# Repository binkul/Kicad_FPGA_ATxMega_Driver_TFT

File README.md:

# Kicad_FPGA_ATxMega_Driver_TFT

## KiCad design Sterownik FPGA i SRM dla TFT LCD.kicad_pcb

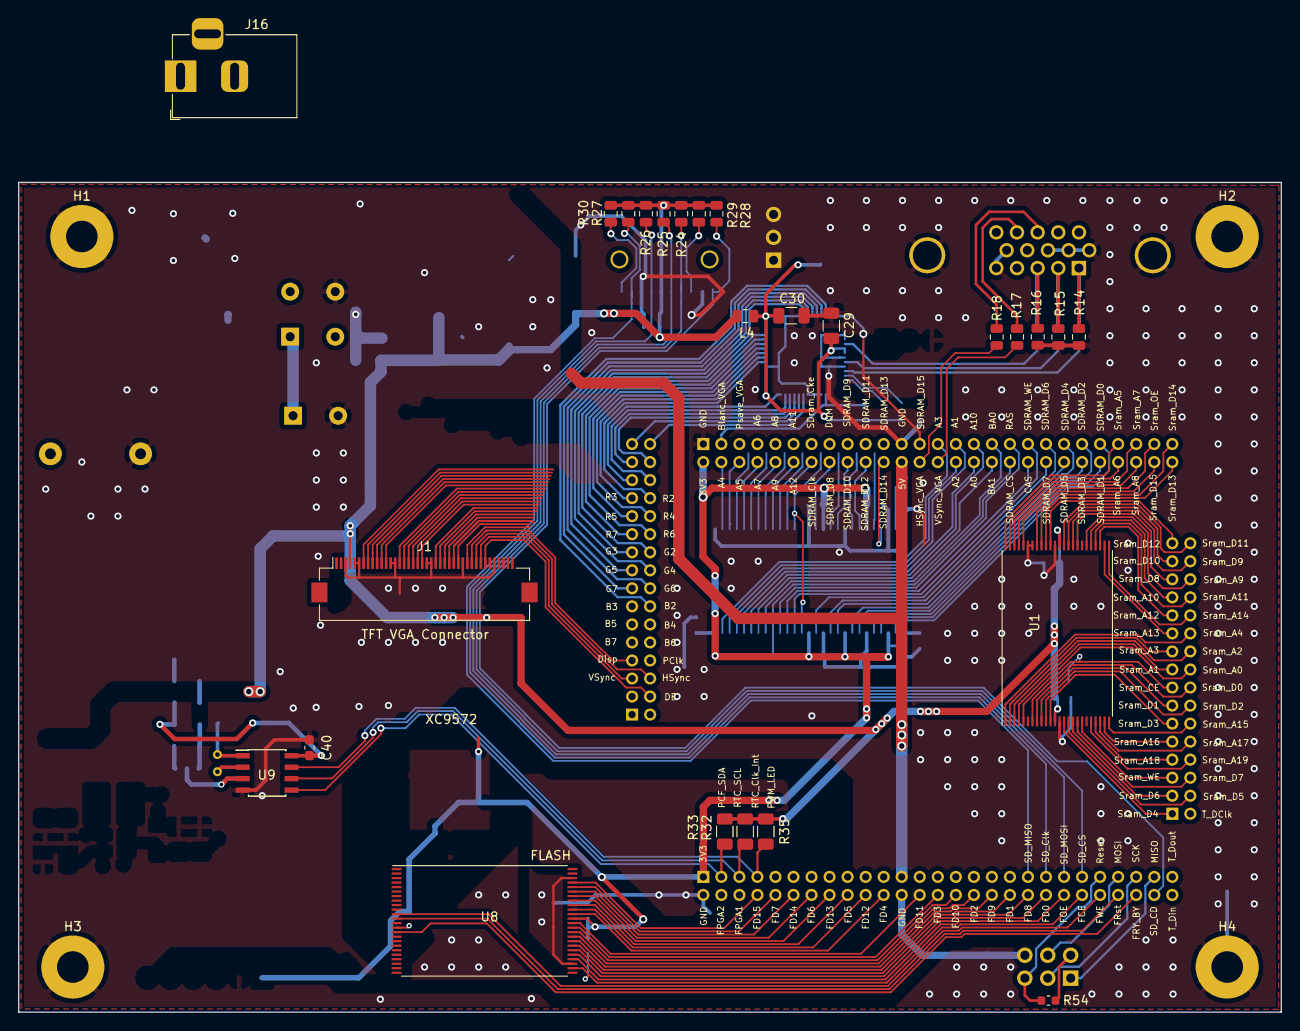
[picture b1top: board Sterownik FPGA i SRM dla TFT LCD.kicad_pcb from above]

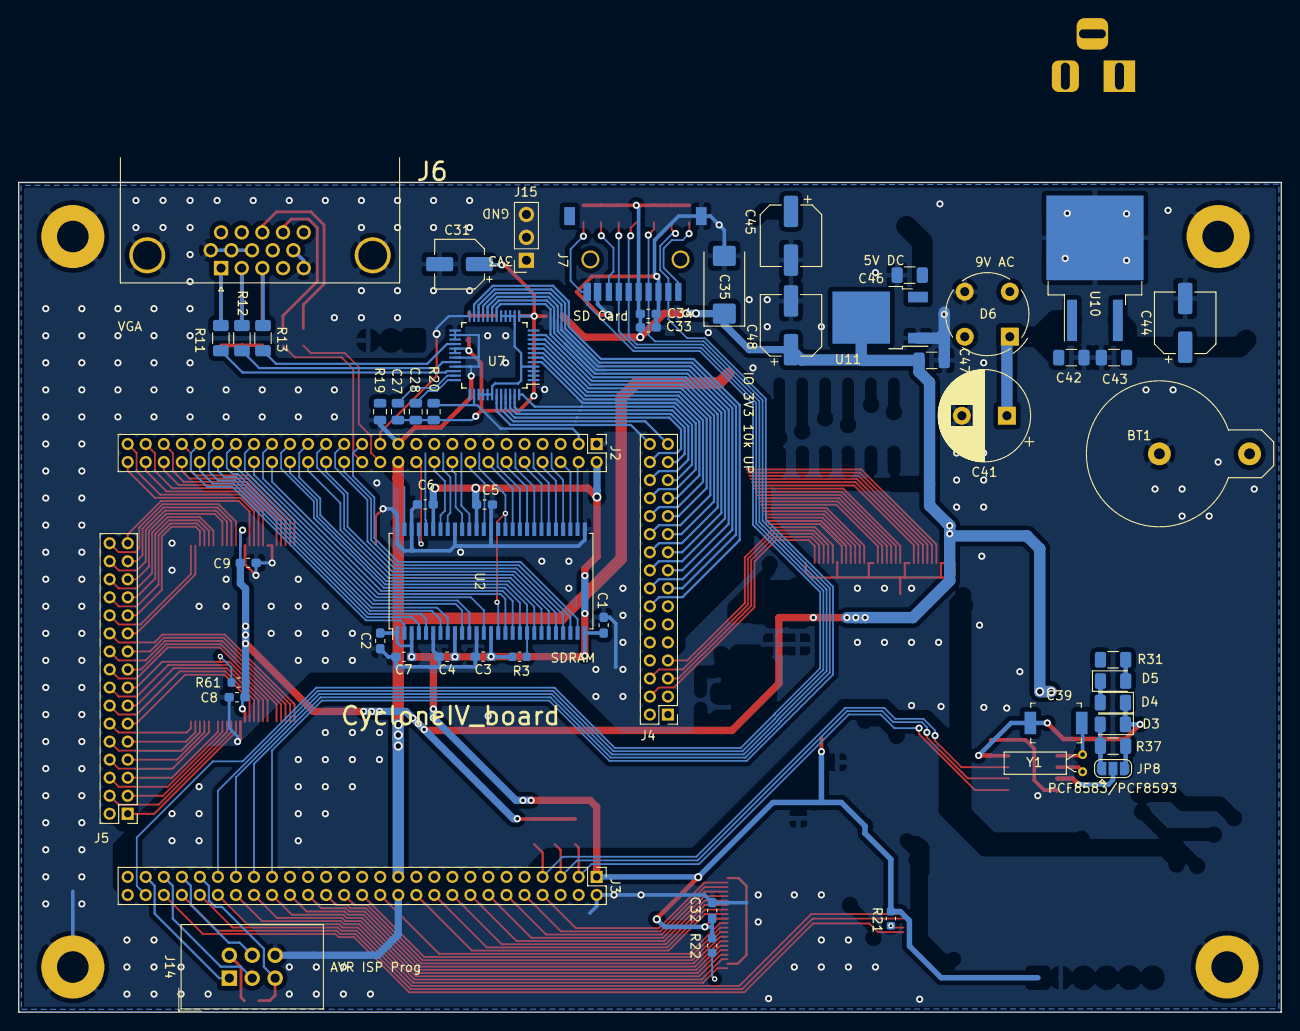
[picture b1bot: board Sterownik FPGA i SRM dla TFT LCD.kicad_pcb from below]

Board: 2 copper layers, 140.0 x 92.0 mm, 84 parts (55 on the bottom side), 167 nets.

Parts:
BT1: Battery_Cell; BatteryHolder_CR1220
C1, C2, C3, C4, C5, C6, C7, C8, C9, C32, C33, C40: 100nF; C_0603_1608Metric_Pad1.05x0.95mm_HandSolder
C27, C28: 100nF; C_0805_2012Metric
C29, C30: 100nF; C_1206_3216Metric
C31: 10uF; CP_Elec_5x5.4
C34: 10nF; C_0603_1608Metric_Pad1.05x0.95mm_HandSolder
C35: 220uF; CP_EIA-7343-40_Kemet-Y_Pad2.25x2.55mm_HandSolder
C39: CTRIM; C_Trimmer_Murata_TZW4
C41: 470uF; CP_Radial_D10.0mm_P5.00mm
C42, C43, C46, C47: 100n; C_1206_3216Metric
C44, C48: 100uF; CP_Elec_6.3x5.7
C45: 220uF; CP_Elec_6.3x5.7
D3, D4, D5: B120-E3; D_1206_3216Metric
D6: B80R; Diode_Bridge_Round_D9.0mm
H1, H2, H3, H4: 3,2mm; MountingHole_3.5mm_Pad
J1: VGA_conn; Hirose_FH12-40S-0.5SH_1x40-1MP_P0.50mm_Horizontal
J2, J3: Conn_02x27_Odd_Even; PinHeader_2x27_P2.00mm_Vertical
J4, J5: Conn_02x16_Odd_Even; PinHeader_2x16_P2.00mm_Vertical
J6: VGA; DSUB-15-HD_Female_Horizontal_P2.29x1.98mm_EdgePinOffset8.35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
J7: Micro_SD_Card; MCC SDMicro
J14: ISP_FPGA; IDC-Header_2x03_P2.54mm_Vertical
J15: RGB_low; PinSocket_1x03_P2.54mm_Vertical
J16: Barrel_Jack_Switch; DC_Jack_14mm
JP8: 8583/8593; SolderJumper-3_P1.3mm_Open_RoundedPad1.0x1.5mm
L4: 10uH; L_0805_2012Metric
R3, R21, R22, R54, R61: 10k; R_0603_1608Metric
R11, R12, R13: 0; R_1206_3216Metric
R14, R15, R16: 75; R_0805_2012Metric
R17, R18: 47; R_0805_2012Metric
R19: 560; R_0805_2012Metric
R20, R24, R25, R26, R27, R28, R29, R30: 10k; R_0805_2012Metric
R31: 1k; R_1206_3216Metric
R32, R33: 4k7; R_1206_3216Metric
R35, R37: 10k; R_1206_3216Metric
U1: SRAM_1024Kx16bit_TSOP48I; TSOP-I-48_18.4x12mm_P0.5mm
U2: SDRAM_16bit_4Mx4bank_TSOP54II; TSOP-II-54_22.2x10.16mm_P0.8mm
U7: ADV7123_TQFP48; TQFP-48_7x7mm_P0.5mm
U8: FLASH_SST38VF6404_TSOP48; TSOP-I-48_18.4x12mm_P0.5mm
U9: PCF8563T; SOIC-8_3.9x4.9mm_P1.27mm
U10: L7805; TO-263-2
U11: LM1117-3.3; TO-252-2
Y1: 32768Hz; Crystal_C26-LF_D2.1mm_L6.5mm_Horizontal

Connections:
+3V3: C8.1, C9.1, C33.1, C34.1, C35.1, C47.1, C48.1, D3.2, J1.4, J7.4, JP8.1, L4.2, R24.2, R25.2, R26.2, R27.2, R28.2, R29.2, R30.2, R32.2, R33.2, R35.2, R37.2, R61.1, U1.12, U1.36, U11.2
+5V: C43.1, C44.1, C45.1, C46.1, J2.24, J3.23, U10.3, U11.3
A0_B: J2.32, U2.23
A1_B: J2.29, U2.24
A2_B: J2.30, U2.25
A3_B: J2.27, U2.26
A4_B: J2.4, U2.29
A5_B: J2.6, U2.30
A6_B: J2.7, U2.31
A7_B: J2.8, U2.32
A8_B: J2.9, U2.33
A9_B: J2.10, U2.34
A10_B: J2.31, U2.22
A11_B: J2.11, U2.35
A12_B: J2.12, U2.36
B2: J1.23, J4.19, U7.18
B3: J1.24, J4.18, U7.19
B4: J1.25, J4.17, U7.20
B5: J1.26, J4.16, U7.21
B6: J1.27, J4.15, U7.22
B7: J1.28, J4.14, U7.23
BA0_B: J2.33, U2.20
BA1_B: J2.34, U2.21
BLANC_VGA: J4.20, U7.11
BLUE_VGA: J6.3, R13.1, R16.2
CAS_B: J2.38, U2.17
CKE_B: J2.13, U2.37
CLK_B: J2.14, U2.38
COMP_VGA: C27.2, U7.35
CS_B: J2.36, R3.2, U2.19
DE: J1.34, J4.4
DISP: J1.31, J4.7
DQ0_B: J2.45, U2.2
DQ1_B: J2.46, U2.4
DQ2_B: J2.43, U2.5
DQ3_B: J2.44, U2.7
DQ4_B: J2.41, U2.8
DQ5_B: J2.42, U2.10
DQ6_B: J2.39, U2.11
DQ7_B: J2.40, U2.13
DQ8_B: J2.16, U2.42
DQ9_B: J2.17, U2.44
DQ10_B: J2.18, U2.45
DQ11_B: J2.19, U2.47
DQ12_B: J2.20, U2.48
DQ13_B: J2.21, U2.50
DQ14_B: J2.22, U2.51
DQM_B: J2.15, U2.15, U2.39
FCE: J3.44, R22.2, U8.26
FD0: J3.40, U8.29
FD1: J3.36, U8.31
FD2: J3.32, U8.33
FD3: J3.28, U8.35
FD4: J3.22, U8.38
FD5: J3.18, U8.40
FD6: J3.14, U8.42
FD7: J3.10, U8.44
FD8: J3.38, U8.30
FD9: J3.34, U8.32
FD10: J3.30, U8.34
FD11: J3.26, U8.36
FD12: J3.20, U8.39
FD13: J3.16, U8.41
FD14: J3.12, U8.43
FD15: J3.8, U8.45
FOE: J3.42, U8.28
FRST: J3.48, U8.12
FRY_BY: J3.50, U8.15
FWE: J3.46, U8.11
FWP: R21.2, U8.14
G2: J1.15, J4.26, U7.5
G3: J1.16, J4.25, U7.6
G4: J1.17, J4.24, U7.7
G5: J1.18, J4.23, U7.8
G6: J1.19, J4.22, U7.9
G7: J1.20, J4.21, U7.10
GND: BT1.2, C1.2, C2.2, C3.2, C4.2, C5.2, C6.2, C7.2, C8.2, C9.2, C29.2, C30.2, C31.2, C32.2, C33.2, C34.2, C35.2, C40.2, C41.2, C42.2, C43.2, C44.2, C45.2, C46.2, C47.2, C48.2, D6.3, H1.1, H2.1, H3.1, H4.1, J1.3, J1.5, J1.6, J1.13, J1.14, J1.21, J1.22, J1.29, J1.36, J2.1, J2.23, J3.2, J3.24, J6.0, J6.5, J6.6, J6.7, J6.8, J6.10, J7.6, J7.9, J7.11, J14.6, J15.3, R14.1, R15.1, R16.1, R19.1, U1.13, U1.37, U1.42, U1.43, U2.6, U2.12, U2.28, U2.41, U2.46, U2.52, U2.54, U7.12, U7.25, U7.26, U7.27, U7.31, U7.33, U8.27, U8.46, U9.4, U10.2, U11.1
GREEN_VGA: J6.2, R12.1, R15.2
HSYNC: J1.32, J4.6
HSYNC_VGA: J6.13, R18.1
HSYNC_VGAI: J2.26, R18.2
ISPMOSI: J3.47, J14.4
ISP_MISO: J3.51, J14.1
ISP_RESET: J3.45, J14.5, R54.1
ISP_SCK: J3.49, J14.3
unnamed: BT1.1, R31.1
unnamed: C39.1, C40.1, D3.1, D4.1, U9.8
unnamed: C39.2, U9.1, Y1.1
unnamed: C41.1, C42.1, D6.1, U10.1
unnamed: D4.2, D5.1
unnamed: D5.2, R31.2
unnamed: D6.2, J16.2
unnamed: D6.4, J16.1
unnamed: R11.2, U7.34
unnamed: R12.2, U7.32
unnamed: R13.2, U7.28
unnamed: U9.2, Y1.2
PCF_8563: JP8.3, R37.1
PCF_SCL: J3.5, R32.1, U9.6
PCF_SDA: J3.3, R33.1, U9.5
PCLK: J1.30, J2.25, U7.24
PSAVE_VGA: J2.3, R20.1, U7.38
R2: J1.7, J4.32, U7.43
R3: J1.8, J4.31, U7.44
R4: J1.9, J4.30, U7.45
R5: J1.10, J4.29, U7.46
R6: J1.11, J4.28, U7.47
R7: J1.12, J4.27, U7.48
RAS_B: J2.35, U2.18
RED_VGA: J6.1, R11.1, R14.2
RGB0: J15.2, U7.1, U7.2, U7.3, U7.4, U7.14, U7.15, U7.16, U7.17, U7.39, U7.40, U7.41, U7.42
RTC_CLK_INT: J3.7, R35.1, U9.7
RTC_INT_A0_RST: JP8.2, U9.3
Rset_VGA: R19.2, U7.37
SD_CD: J3.52, J7.10, R28.1
SD_CLK: J3.39, J7.5, R26.1
SD_CS: J3.43, J7.2, R24.1
SD_MISO: J3.37, J7.7, R27.1
SD_MOSI: J3.41, J7.3, R25.1
SD_NC1: J7.1, R29.1
SD_NC2: J7.8, R30.1
Sram_A0: J5.18, U1.5
Sram_A1: J5.17, U1.4
Sram_A2: J5.20, U1.3
Sram_A3: J5.19, U1.2
Sram_A4: J5.22, U1.1
Sram_A5: J2.47, U1.48
Sram_A6: J2.48, U1.47
Sram_A7: J2.49, U1.46
Sram_A8: J2.50, U1.45
Sram_A9: J5.28, U1.30
Sram_A10: J5.25, U1.29
Sram_A11: J5.26, U1.28
Sram_A12: J5.23, U1.27
Sram_A13: J5.21, U1.26
Sram_A14: J5.24, U1.25
Sram_A15: J5.12, U1.24
Sram_A16: J5.9, U1.23
Sram_A17: J5.10, U1.22
Sram_A18: J5.7, U1.21
Sram_A19: J5.8, U1.20
Sram_CE: J5.15, R61.2, U1.7
Sram_D0: J5.16, U1.8
Sram_D1: J5.13, U1.9
Sram_D2: J5.14, U1.10
Sram_D3: J5.11, U1.11
Sram_D4: J5.1, U1.14
Sram_D5: J5.4, U1.15
Sram_D6: J5.3, U1.16
Sram_D7: J5.6, U1.17
Sram_D8: J5.27, U1.32
Sram_D9: J5.30, U1.33
Sram_D10: J5.29, U1.34
Sram_D11: J5.32, U1.35
Sram_D12: J5.31, U1.38
Sram_D13: J2.54, U1.39
Sram_D14: J2.53, U1.40
Sram_D15: J2.52, U1.41
Sram_OE: J2.51, U1.44
Sram_WE: J5.5, U1.18
VAA: C27.1, C28.1, C29.1, C30.1, C31.1, J15.1, L4.1, R20.2, U7.13, U7.29, U7.30
VCC: C1.1, C2.1, C3.1, C4.1, C5.1, C6.1, C7.1, C32.1, J2.2, J3.1, J14.2, R3.1, R21.1, R22.1, R54.2, U2.1, U2.3, U2.9, U2.14, U2.27, U2.43, U2.49, U8.37
VSYNC: J1.33, J4.5
VSYNC_VGA: J6.14, R17.1
VSYNC_VGAI: J2.28, R17.2
Vref_VGA: C28.2, U7.36
WE_B: J2.37, U2.16
